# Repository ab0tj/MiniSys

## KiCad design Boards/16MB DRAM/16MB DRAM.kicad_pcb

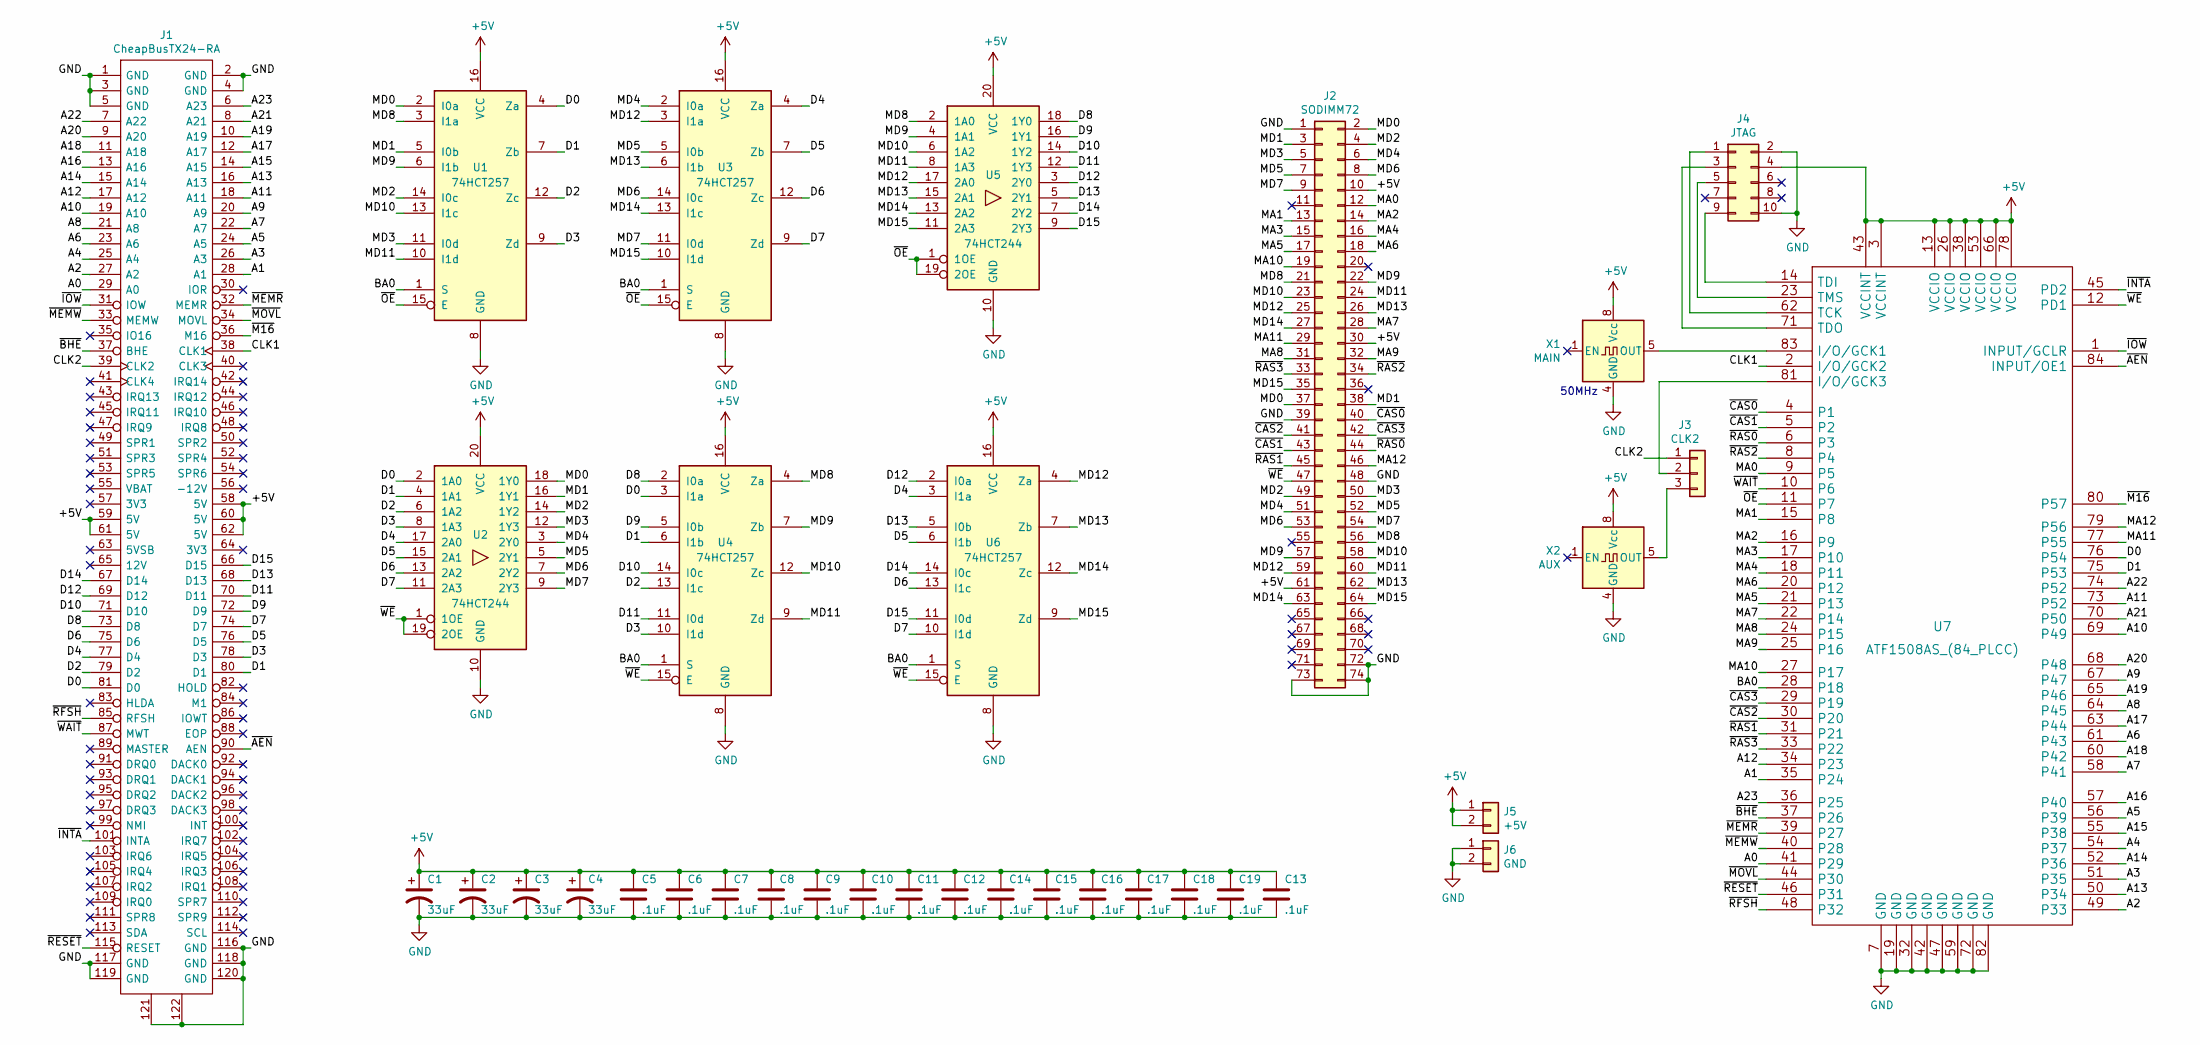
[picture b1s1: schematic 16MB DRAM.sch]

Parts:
C1, C2, C3, C4: 33uF; CP_Tantalum_Case-B_EIA-3528-21_Hand
C5, C6, C7, C8, C9, C10, C11, C12, C13, C14, C15, C16, C17, C18, C19: .1uF; C_0805_HandSoldering
J1: CheapBusTX24-RA; JAE_TX24-120R-LT-H1E; Mouser Part Number 656-TX24120RLTH1E
J2: SODIMM72; SODIMM-72
J3: CLK2; Pin_Header_Straight_1x03_Pitch2.54mm
J4: JTAG; Pin_Header_Straight_2x05_Pitch2.54mm
J5: +5V; Pin_Header_Straight_1x02_Pitch2.54mm
J6: GND; Pin_Header_Straight_1x02_Pitch2.54mm
U1, U3, U4, U6: 74HCT257; SOIC-16_3.9x9.9mm_Pitch1.27mm
U2, U5: 74HCT244; SOIC-20W_7.5x12.8mm_Pitch1.27mm
U7: ATF1508AS_(84_PLCC); PLCC84
X1: MAIN; Oscillator_DIP-8
X2: AUX; Oscillator_DIP-8

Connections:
+5V: C1.1, C2.1, C3.1, C4.1, C5.1, C6.1, C7.1, C8.1, C9.1, C10.1, C11.1, C12.1, C13.1, C14.1, C15.1, C16.1, C17.1, C18.1, C19.1, J1.58 (5V), J1.59 (5V), J1.60 (5V), J1.61 (5V), J1.62 (5V), J2.10, J2.30, J2.61, J4.4, J5.1, J5.2, U1.16 (VCC), U2.20 (VCC), U3.16 (VCC), U4.16 (VCC), U5.20 (VCC), U6.16 (VCC), U7.3 (VCCINT), U7.13 (VCCIO), U7.26 (VCCIO), U7.38 (VCCIO), U7.43 (VCCINT), U7.53 (VCCIO), U7.66 (VCCIO), U7.78 (VCCIO), X1.8 (Vcc), X2.8 (Vcc)
/A0: J1.29 (A0), U7.41 (P29)
/A1: J1.28 (A1), U7.35 (P24)
/A2: J1.27 (A2), U7.49 (P33)
/A3: J1.26 (A3), U7.51 (P35)
/A4: J1.25 (A4), U7.54 (P37)
/A5: J1.24 (A5), U7.56 (P39)
/A6: J1.23 (A6), U7.61 (P43)
/A7: J1.22 (A7), U7.58 (P41)
/A8: J1.21 (A8), U7.64 (P45)
/A9: J1.20 (A9), U7.67 (P47)
/A10: J1.19 (A10), U7.69 (P49)
/A11: J1.18 (A11), U7.73 (P52)
/A12: J1.17 (A12), U7.34 (P23)
/A13: J1.16 (A13), U7.50 (P34)
/A14: J1.15 (A14), U7.52 (P36)
/A15: J1.14 (A15), U7.55 (P38)
/A16: J1.13 (A16), U7.57 (P40)
/A17: J1.12 (A17), U7.63 (P44)
/A18: J1.11 (A18), U7.60 (P42)
/A19: J1.10 (A19), U7.65 (P46)
/A20: J1.9 (A20), U7.68 (P48)
/A21: J1.8 (A21), U7.70 (P50)
/A22: J1.7 (A22), U7.74 (P52)
/A23: J1.6 (A23), U7.36 (P25)
/BA0: U1.1 (S), U3.1 (S), U4.1 (S), U6.1 (S), U7.28 (P18)
/CLK1: J1.38 (CLK1), U7.2 (I/O/GCK2)
/CLK2: J1.39 (CLK2), J3.1
/D0: J1.81 (D0), U1.4 (Za), U2.2 (1A0), U4.3 (I1a), U7.76 (P54)
/D1: J1.80 (D1), U1.7 (Zb), U2.4 (1A1), U4.6 (I1b), U7.75 (P53)
/D2: J1.79 (D2), U1.12 (Zc), U2.6 (1A2), U4.13 (I1c)
/D3: J1.78 (D3), U1.9 (Zd), U2.8 (1A3), U4.10 (I1d)
/D4: J1.77 (D4), U2.17 (2A0), U3.4 (Za), U6.3 (I1a)
/D5: J1.76 (D5), U2.15 (2A1), U3.7 (Zb), U6.6 (I1b)
/D6: J1.75 (D6), U2.13 (2A2), U3.12 (Zc), U6.13 (I1c)
/D7: J1.74 (D7), U2.11 (2A3), U3.9 (Zd), U6.10 (I1d)
/D8: J1.73 (D8), U4.2 (I0a), U5.18 (1Y0)
/D9: J1.72 (D9), U4.5 (I0b), U5.16 (1Y1)
/D10: J1.71 (D10), U4.14 (I0c), U5.14 (1Y2)
/D11: J1.70 (D11), U4.11 (I0d), U5.12 (1Y3)
/D12: J1.69 (D12), U5.3 (2Y0), U6.2 (I0a)
/D13: J1.68 (D13), U5.5 (2Y1), U6.5 (I0b)
/D14: J1.67 (D14), U5.7 (2Y2), U6.14 (I0c)
/D15: J1.66 (D15), U5.9 (2Y3), U6.11 (I0d)
/MA0: J2.12, U7.9 (P5)
/MA1: J2.13, U7.15 (P8)
/MA2: J2.14, U7.16 (P9)
/MA3: J2.15, U7.17 (P10)
/MA4: J2.16, U7.18 (P11)
/MA5: J2.17, U7.21 (P13)
/MA6: J2.18, U7.20 (P12)
/MA7: J2.28, U7.22 (P14)
/MA8: J2.31, U7.24 (P15)
/MA9: J2.32, U7.25 (P16)
/MA10: J2.19, U7.27 (P17)
/MA11: J2.29, U7.77 (P55)
/MA12: J2.46, U7.79 (P56)
/MD0: J2.2, J2.37, U1.2 (I0a), U2.18 (1Y0)
/MD1: J2.3, J2.38, U1.5 (I0b), U2.16 (1Y1)
/MD2: J2.4, J2.49, U1.14 (I0c), U2.14 (1Y2)
/MD3: J2.5, J2.50, U1.11 (I0d), U2.12 (1Y3)
/MD4: J2.6, J2.51, U2.3 (2Y0), U3.2 (I0a)
/MD5: J2.7, J2.52, U2.5 (2Y1), U3.5 (I0b)
/MD6: J2.8, J2.53, U2.7 (2Y2), U3.14 (I0c)
/MD7: J2.9, J2.54, U2.9 (2Y3), U3.11 (I0d)
/MD8: J2.21, J2.56, U1.3 (I1a), U4.4 (Za), U5.2 (1A0)
/MD9: J2.22, J2.57, U1.6 (I1b), U4.7 (Zb), U5.4 (1A1)
/MD10: J2.23, J2.58, U1.13 (I1c), U4.12 (Zc), U5.6 (1A2)
/MD11: J2.24, J2.60, U1.10 (I1d), U4.9 (Zd), U5.8 (1A3)
/MD12: J2.25, J2.59, U3.3 (I1a), U5.17 (2A0), U6.4 (Za)
/MD13: J2.26, J2.62, U3.6 (I1b), U5.15 (2A1), U6.7 (Zb)
/MD14: J2.27, J2.63, U3.13 (I1c), U5.13 (2A2), U6.12 (Zc)
/MD15: J2.35, J2.64, U3.10 (I1d), U5.11 (2A3), U6.9 (Zd)
/~AEN: J1.90 (AEN), U7.84 (INPUT/OE1)
/~BHE: J1.37 (BHE), U7.37 (P26)
/~CAS0: J2.40, U7.4 (P1)
/~CAS1: J2.43, U7.5 (P2)
/~CAS2: J2.41, U7.30 (P20)
/~CAS3: J2.42, U7.29 (P19)
/~INTA: J1.101 (INTA), U7.45 (PD2)
/~IOW: J1.31 (IOW), U7.1 (INPUT/GCLR)
/~M16: J1.36 (M16), U7.80 (P57)
/~MEMR: J1.32 (MEMR), U7.39 (P27)
/~MEMW: J1.33 (MEMW), U7.40 (P28)
/~MOVL: J1.34 (MOVL), U7.44 (P30)
/~OE: U1.15 (E), U3.15 (E), U5.1 (1OE), U5.19 (2OE), U7.11 (P7)
/~RAS0: J2.44, U7.6 (P3)
/~RAS1: J2.45, U7.31 (P21)
/~RAS2: J2.34, U7.8 (P4)
/~RAS3: J2.33, U7.33 (P22)
/~RESET: J1.115 (RESET), U7.46 (P31)
/~RFSH: J1.85 (RFSH), U7.48 (P32)
/~WAIT: J1.87 (MWT), U7.10 (P6)
/~WE: J2.47, U2.1 (1OE), U2.19 (2OE), U4.15 (E), U6.15 (E), U7.12 (PD1)
GND: C1.2, C2.2, C3.2, C4.2, C5.2, C6.2, C7.2, C8.2, C9.2, C10.2, C11.2, C12.2, C13.2, C14.2, C15.2, C16.2, C17.2, C18.2, C19.2, J1.1 (GND), J1.2 (GND), J1.3 (GND), J1.4 (GND), J1.5 (GND), J1.116 (GND), J1.117 (GND), J1.118 (GND), J1.119 (GND), J1.120 (GND), J1.121, J1.122, J2.1, J2.39, J2.48, J2.72, J2.73, J2.74, J4.2, J4.10, J6.1, J6.2, U1.8 (GND), U2.10 (GND), U3.8 (GND), U4.8 (GND), U5.10 (GND), U6.8 (GND), U7.7 (GND), U7.19 (GND), U7.32 (GND), U7.42 (GND), U7.47 (GND), U7.59 (GND), U7.72 (GND), U7.82 (GND), X1.4 (GND), X2.4 (GND)
unnamed: J3.2, U7.81 (I/O/GCK3)
unnamed: J3.3, X2.5 (OUT)
unnamed: J4.1, U7.62 (TCK)
unnamed: J4.3, U7.71 (TDO)
unnamed: J4.5, U7.23 (TMS)
unnamed: J4.9, U7.14 (TDI)
unnamed: U7.83 (I/O/GCK1), X1.5 (OUT)

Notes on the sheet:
50MHz

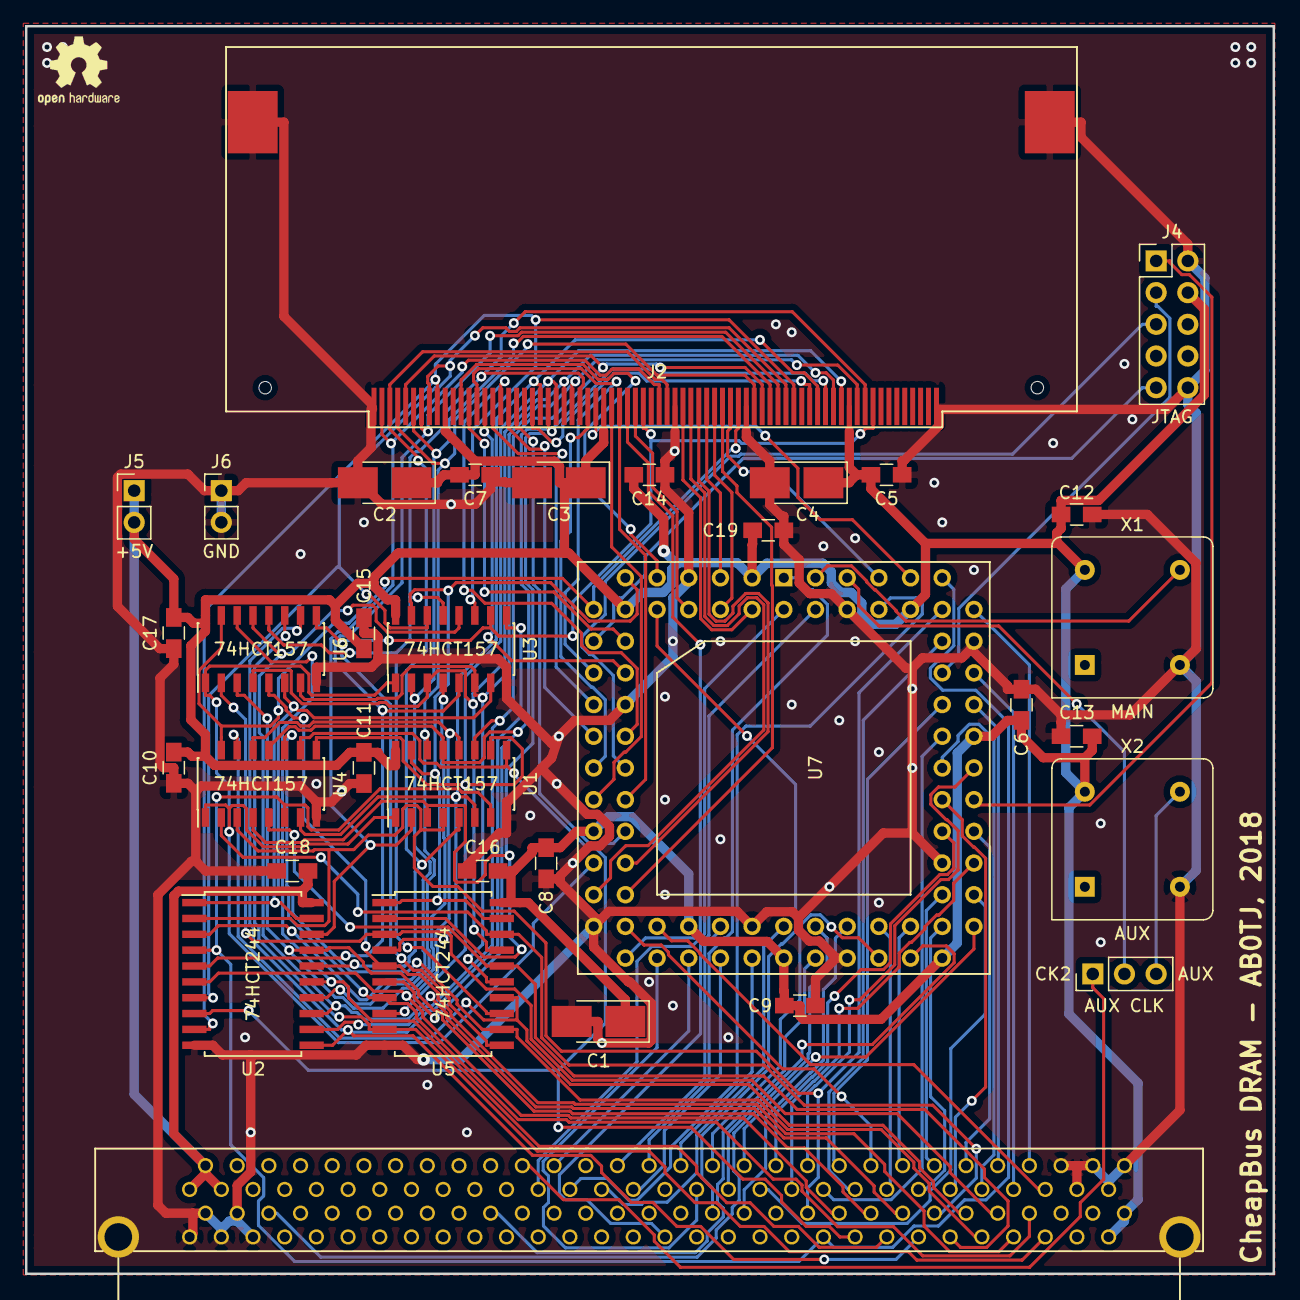
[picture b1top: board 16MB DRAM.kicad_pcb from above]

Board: 2 copper layers, 100.0 x 100.0 mm, 34 parts (0 on the bottom side), 102 nets.
